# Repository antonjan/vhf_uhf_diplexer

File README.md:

# vhf_uhf_diplexer
This is all the files for a VHF /UHF Diplexer 10w max<br>
<br>
PCB layout
<br>
# Parts
https://www.mouser.com/ProjectManager/ProjectDetail.aspx?AccessID=959491BFAB

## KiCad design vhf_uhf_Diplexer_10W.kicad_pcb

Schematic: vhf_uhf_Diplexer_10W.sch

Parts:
C1, C2: 18pF; C_1206_HandSoldering
C3, C5: 4.7pF; C_1206_HandSoldering
C4: 2.7pF; C_1206_HandSoldering
J1, J2, J3, J4: 3mm mount; MountingHole_3.2mm_M3_Pad
L1, L3: 68nH; SMD-2520
L2: 100nH; SMD-2520
L4, L5: 15nH; SMD-2520
P1, P2, P3: SMA; SMA_Edge

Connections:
GND: C1.2, C2.2, J1.1, J2.1, J3.1, J4.1, L4.1, L5.1, P1.2, P2.2, P3.2
unnamed: C1.1, L1.1, L2.2
unnamed: C2.1, L2.1, L3.2
unnamed: C3.1, C4.2, L4.2
unnamed: C3.2, L1.2, P1.1
unnamed: C4.1, C5.2, L5.2
unnamed: C5.1, P2.1
unnamed: L3.1, P3.1

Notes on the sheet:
70cm
Common

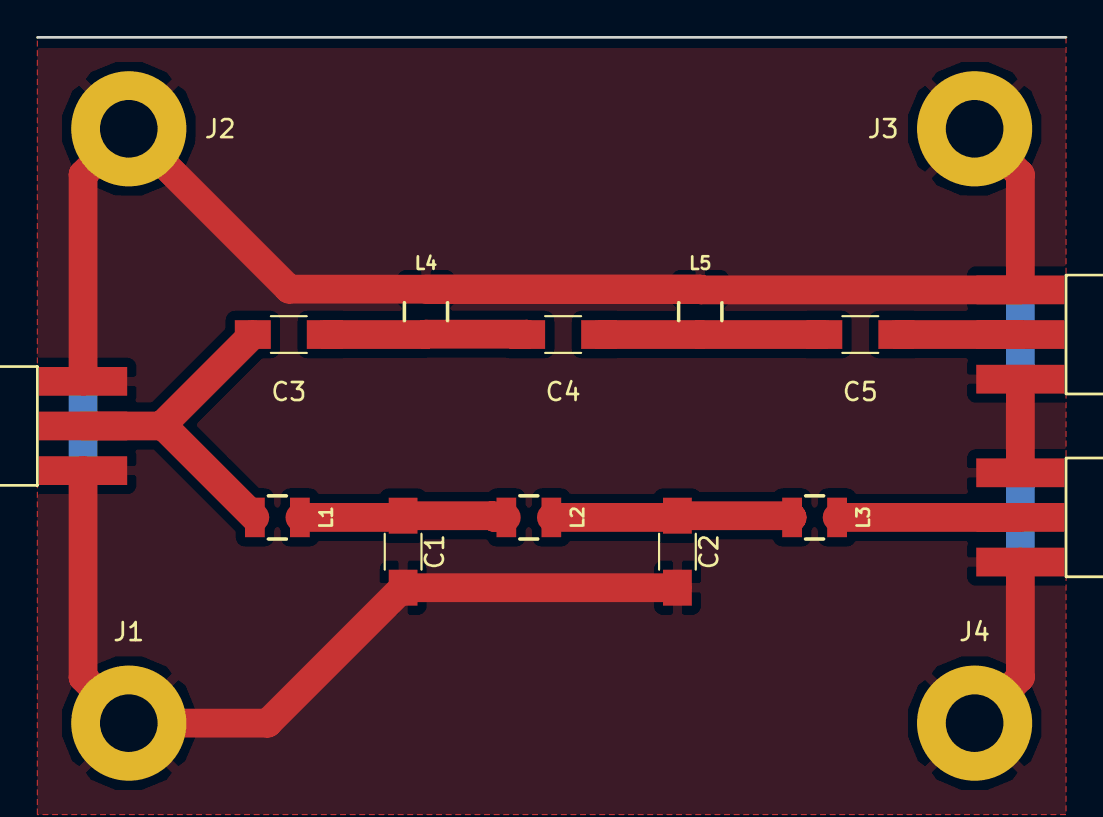
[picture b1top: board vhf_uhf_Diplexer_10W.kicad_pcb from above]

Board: 2 copper layers, 17 parts (0 on the bottom side), 8 nets.

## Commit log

2018-01-13 Diagram
2018-01-13 Added images of similations
2018-01-13 Added kicad diagram
2018-01-13 update kad diagram
2018-01-14 added part list
2018-01-14 Created PCB with Componenets
2018-01-14 Added sma to bom
2018-01-15 fixed bug with map not displaying
2018-01-15 removed html directory
2018-01-15 adding pdf dokumets
2018-02-08 added Diagram picture
2018-02-08 PCB picture
2018-02-08 Added PCb image
2018-08-03 Added Dimentions to Picture
2018-08-03 change diagram
2020-03-20 adding parts list
2022-01-19 Added VNA Images and updated inductor footprints
